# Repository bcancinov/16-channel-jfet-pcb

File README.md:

# 16-channel-jfet-pcb
16 Channel JFET Board 6-layer PCB designed with KiCAD 9.0 used for Skipper II project at NOIRLab.

This design uses LSJ689 P-JFET in common-drain or source follower configuration.

Designed by Braulio Cancino - braulio.cancino@noirlab.edu

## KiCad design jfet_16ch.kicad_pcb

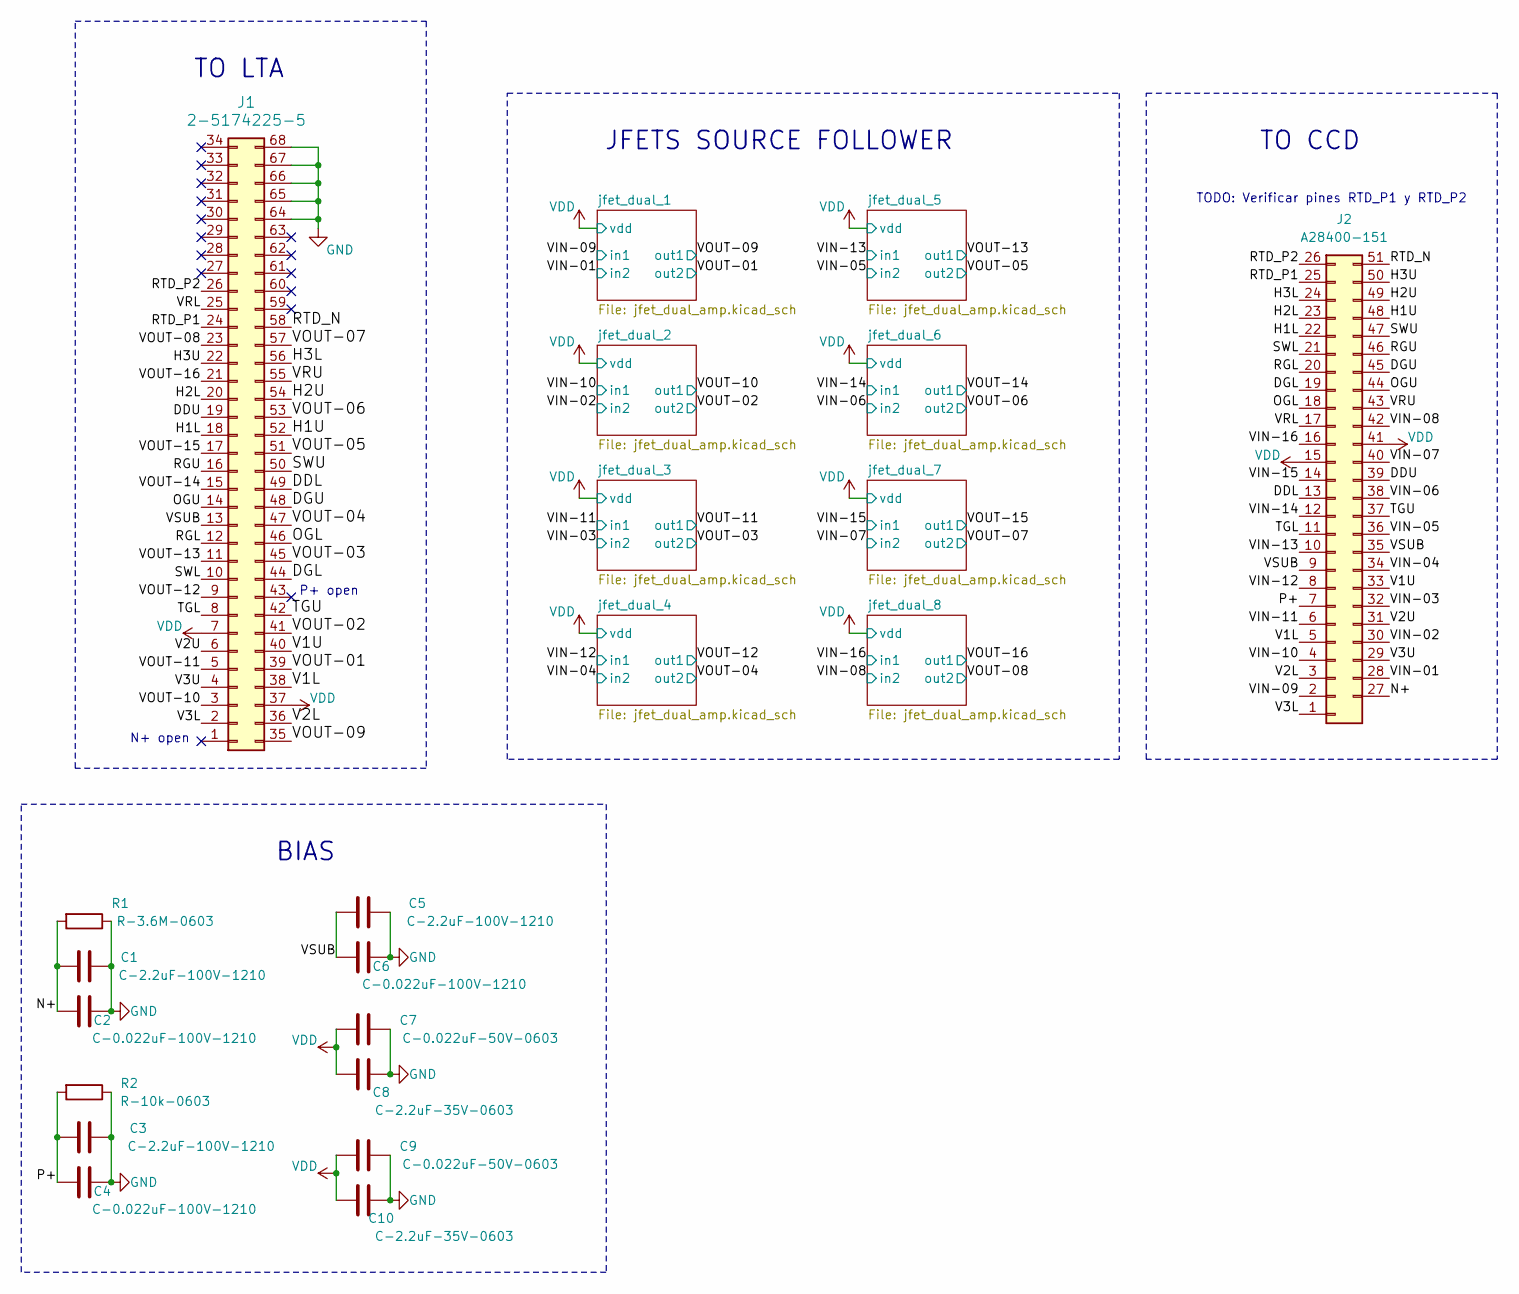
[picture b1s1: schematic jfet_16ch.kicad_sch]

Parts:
C1, C3, C5: C-2.2uF-100V-1210; C_1210_3225Metric; Manufacturer# C1210C225K1RACAUTO; Digikey 399-13375-2-ND
C2, C4, C6: C-0.022uF-100V-1210; C_1210_3225Metric; Manufacturer# C3225C0G2A223J160AA; Digikey 445-2347-1-ND
C7, C9: C-0.022uF-50V-0603; C_0603_1608Metric; Manufacturer# C0603C223J5RAC7867; Digikey 399-C0603C223J5RAC7867CT-ND
C8, C10: C-2.2uF-35V-0603; C_0603_1608Metric; Manufacturer# GRM188R6YA225MA12D; Digikey 490-10486-6-ND
J1: 2-5174225-5; Manufacturer# 2-5174225-5; Digikey A33476-ND
J2: A28400-151; Manufacturer# A28400-151
R1: R-3.6M-0603; R_0603_1608Metric; Manufacturer# ERJ-3GEYJ365V; Digikey P3.6MGCT-ND
R2: R-10k-0603; R_0603_1608Metric; Manufacturer# RT0603BRD0710KL; Digikey YAG1236CT-ND

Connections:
/DDL: J1.49, J2.13
/DDU: J1.19, J2.39
/DGL: J1.44, J2.19
/DGU: J1.48, J2.45
/H1L: J1.18, J2.22
/H1U: J1.52, J2.48
/H2L: J1.20, J2.23
/H2U: J1.54, J2.49
/H3L: J1.56, J2.24
/H3U: J1.22, J2.50
/N+: C1.2, C2.2, J2.27, R1.2
/OGL: J1.46, J2.18
/OGU: J1.14, J2.44
/P+: C3.2, C4.2, J2.7, R2.2
/RGL: J1.12, J2.20
/RGU: J1.16, J2.46
/RTD_N: J1.58, J2.51
/RTD_P1: J1.24, J2.25
/RTD_P2: J1.26, J2.26
/SWL: J1.10, J2.21
/SWU: J1.50, J2.47
/TGL: J1.8, J2.11
/TGU: J1.42, J2.37
/V1L: J1.38, J2.5
/V1U: J1.40, J2.33
/V2L: J1.36, J2.3
/V2U: J1.6, J2.31
/V3L: J1.2, J2.1
/V3U: J1.4, J2.29
/VIN-01: J2.28; also elsewhere on the board
/VIN-02: J2.30; also elsewhere on the board
/VIN-03: J2.32; also elsewhere on the board
/VIN-04: J2.34; also elsewhere on the board
/VIN-05: J2.36; also elsewhere on the board
/VIN-06: J2.38; also elsewhere on the board
/VIN-07: J2.40; also elsewhere on the board
/VIN-08: J2.42; also elsewhere on the board
/VIN-09: J2.2; also elsewhere on the board
/VIN-10: J2.4; also elsewhere on the board
/VIN-11: J2.6; also elsewhere on the board
/VIN-12: J2.8; also elsewhere on the board
/VIN-13: J2.10; also elsewhere on the board
/VIN-14: J2.12; also elsewhere on the board
/VIN-15: J2.14; also elsewhere on the board
/VIN-16: J2.16; also elsewhere on the board
/VOUT-01: J1.39; also elsewhere on the board
/VOUT-02: J1.41; also elsewhere on the board
/VOUT-03: J1.45; also elsewhere on the board
/VOUT-04: J1.47; also elsewhere on the board
/VOUT-05: J1.51; also elsewhere on the board
/VOUT-06: J1.53; also elsewhere on the board
/VOUT-07: J1.57; also elsewhere on the board
/VOUT-08: J1.23; also elsewhere on the board
/VOUT-09: J1.35; also elsewhere on the board
/VOUT-10: J1.3; also elsewhere on the board
/VOUT-11: J1.5; also elsewhere on the board
/VOUT-12: J1.9; also elsewhere on the board
/VOUT-13: J1.11; also elsewhere on the board
/VOUT-14: J1.15; also elsewhere on the board
/VOUT-15: J1.17; also elsewhere on the board
/VOUT-16: J1.21; also elsewhere on the board
/VRL: J1.25, J2.17
/VRU: J1.55, J2.43
/VSUB: C5.2, C6.2, J1.13, J2.9, J2.35
GND: C1.1, C2.1, C3.1, C4.1, C5.1, C6.1, C7.1, C8.1, C9.1, C10.1, J1.64, J1.65, J1.66, J1.67, J1.68, R1.1, R2.1; also elsewhere on the board
VDD: C7.2, C8.2, C9.2, C10.2, J1.7, J1.37, J2.15, J2.41; also elsewhere on the board

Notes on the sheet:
BIAS
TO LTA
N+ open
P+ open
TO CCD
JFETS SOURCE FOLLOWER
TODO: Verificar pines RTD_P1 y RTD_P2

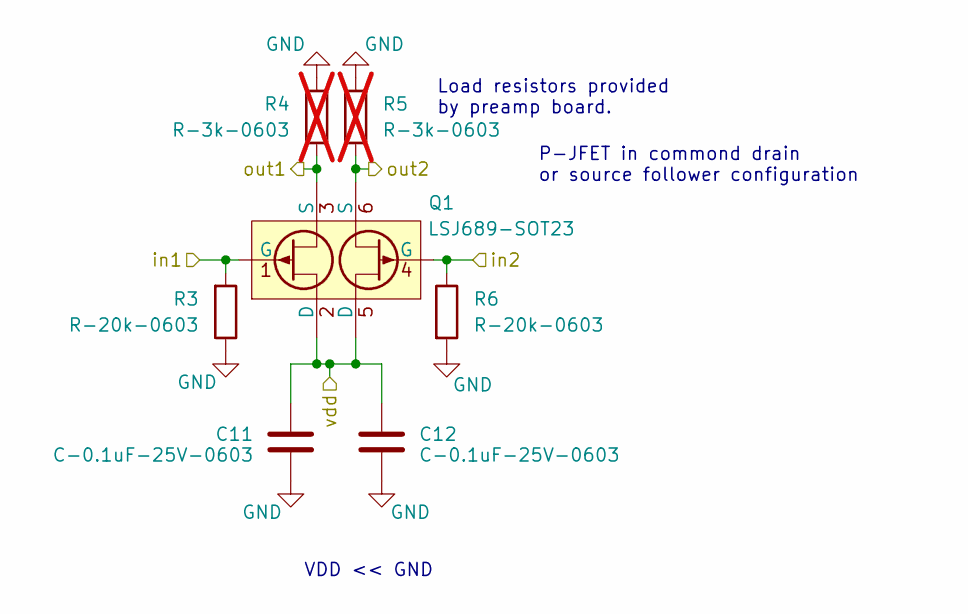
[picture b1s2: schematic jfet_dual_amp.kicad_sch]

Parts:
C11, C12: C-0.1uF-25V-0603; C_0603_1608Metric; Manufacturer# CL10B104KB8NNWC; Digikey 1276-1935-1-ND
Q1: LSJ689-SOT23; SOT-23-6
R3, R6: R-20k-0603; R_0603_1608Metric; Manufacturer# MCT06030C2002FP500; Digikey MCT0603-20.0K-CFCT-ND
R4, R5: R-3k-0603; R_0603_1608Metric; Manufacturer# MCT06030C3001FP500; Digikey MCT0603-3.00K-CFCT-ND; not fitted

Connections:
/VIN-01: Q1.4 (G), R6.1; also elsewhere on the board
/VIN-09: Q1.1 (G), R3.2; also elsewhere on the board
/VOUT-01: Q1.6 (S), R5.1; also elsewhere on the board
/VOUT-09: Q1.3 (S), R4.1; also elsewhere on the board
GND: C11.1, C12.1, R3.1, R4.2, R5.2, R6.2; also elsewhere on the board
VDD: C11.2, C12.2, Q1.2 (D), Q1.5 (D); also elsewhere on the board

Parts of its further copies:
C13, C14, C15, C16, C17, C18, C19, C20, C21, C22, C23, C24, C25, C26: C-0.1uF-25V-0603; C_0603_1608Metric; Manufacturer# CL10B104KB8NNWC; Digikey 1276-1935-1-ND
Q2, Q3, Q4, Q5, Q6, Q7, Q8: LSJ689-SOT23; SOT-23-6
R7, R10, R11, R14, R15, R18, R19, R22, R23, R26, R27, R30, R31, R34: R-20k-0603; R_0603_1608Metric; Manufacturer# MCT06030C2002FP500; Digikey MCT0603-20.0K-CFCT-ND
R8, R9, R12, R13, R16, R17, R20, R21, R24, R25, R28, R29, R32, R33: R-3k-0603; R_0603_1608Metric; Manufacturer# MCT06030C3001FP500; Digikey MCT0603-3.00K-CFCT-ND; not fitted

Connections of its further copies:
/VIN-02: Q2.4 (G), R10.1; also elsewhere on the board
/VIN-03: Q3.4 (G), R14.1; also elsewhere on the board
/VIN-04: Q4.4 (G), R18.1; also elsewhere on the board
/VIN-05: Q5.4 (G), R22.1; also elsewhere on the board
/VIN-06: Q6.4 (G), R26.1; also elsewhere on the board
/VIN-07: Q7.4 (G), R30.1; also elsewhere on the board
/VIN-08: Q8.4 (G), R34.1; also elsewhere on the board
/VIN-10: Q2.1 (G), R7.2; also elsewhere on the board
/VIN-11: Q3.1 (G), R11.2; also elsewhere on the board
/VIN-12: Q4.1 (G), R15.2; also elsewhere on the board
/VIN-13: Q5.1 (G), R19.2; also elsewhere on the board
/VIN-14: Q6.1 (G), R23.2; also elsewhere on the board
/VIN-15: Q7.1 (G), R27.2; also elsewhere on the board
/VIN-16: Q8.1 (G), R31.2; also elsewhere on the board
/VOUT-02: Q2.6 (S), R9.1; also elsewhere on the board
/VOUT-03: Q3.6 (S), R13.1; also elsewhere on the board
/VOUT-04: Q4.6 (S), R17.1; also elsewhere on the board
/VOUT-05: Q5.6 (S), R21.1; also elsewhere on the board
/VOUT-06: Q6.6 (S), R25.1; also elsewhere on the board
/VOUT-07: Q7.6 (S), R29.1; also elsewhere on the board
/VOUT-08: Q8.6 (S), R33.1; also elsewhere on the board
/VOUT-10: Q2.3 (S), R8.1; also elsewhere on the board
/VOUT-11: Q3.3 (S), R12.1; also elsewhere on the board
/VOUT-12: Q4.3 (S), R16.1; also elsewhere on the board
/VOUT-13: Q5.3 (S), R20.1; also elsewhere on the board
/VOUT-14: Q6.3 (S), R24.1; also elsewhere on the board
/VOUT-15: Q7.3 (S), R28.1; also elsewhere on the board
/VOUT-16: Q8.3 (S), R32.1; also elsewhere on the board
GND: C13.1, C14.1, C15.1, C16.1, C17.1, C18.1, C19.1, C20.1, C21.1, C22.1, C23.1, C24.1, C25.1, C26.1, R7.1, R8.2, R9.2, R10.2, R11.1, R12.2, R13.2, R14.2, R15.1, R16.2, R17.2, R18.2, R19.1, R20.2, R21.2, R22.2, R23.1, R24.2, R25.2, R26.2, R27.1, R28.2, R29.2, R30.2, R31.1, R32.2, R33.2, R34.2; also elsewhere on the board
VDD: C13.2, C14.2, C15.2, C16.2, C17.2, C18.2, C19.2, C20.2, C21.2, C22.2, C23.2, C24.2, C25.2, C26.2, Q2.2 (D), Q2.5 (D), Q3.2 (D), Q3.5 (D), Q4.2 (D), Q4.5 (D), Q5.2 (D), Q5.5 (D), Q6.2 (D), Q6.5 (D), Q7.2 (D), Q7.5 (D), Q8.2 (D), Q8.5 (D); also elsewhere on the board

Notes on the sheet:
P-JFET in commond drain or source follower configuration
VDD << GND
Load resistors provided by preamp board.

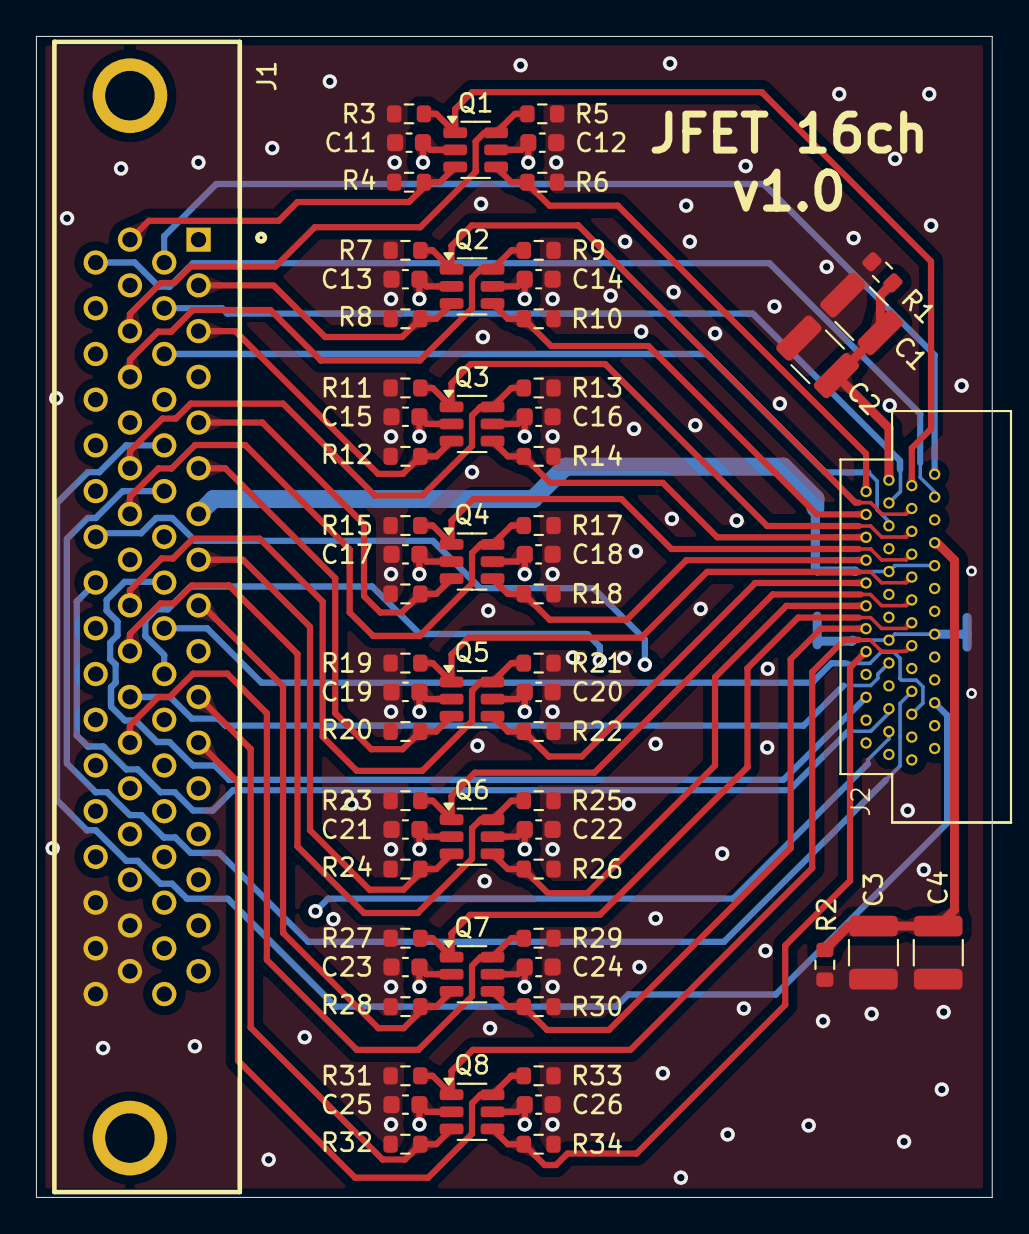
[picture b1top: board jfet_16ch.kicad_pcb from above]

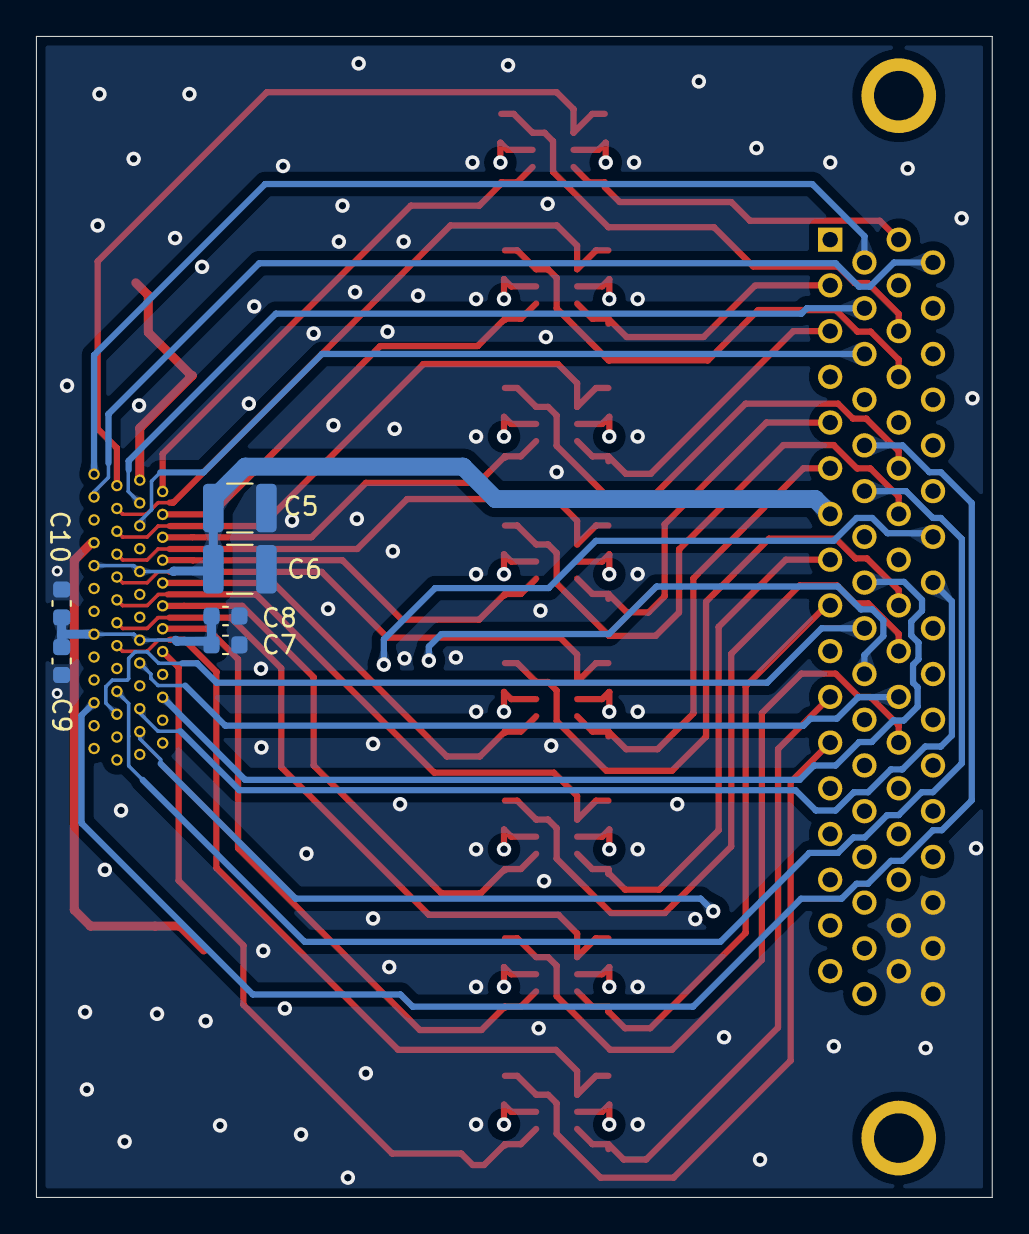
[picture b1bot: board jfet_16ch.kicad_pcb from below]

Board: 6 copper layers, 53.1 x 64.5 mm, 70 parts (6 on the bottom side), 66 nets.

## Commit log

2025-08-29 First upload
2025-08-29 edit
